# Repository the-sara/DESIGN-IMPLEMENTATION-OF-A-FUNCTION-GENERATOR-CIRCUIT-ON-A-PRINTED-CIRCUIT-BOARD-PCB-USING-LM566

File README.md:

Function Generator (PCB with LM566): Designed and built a function generator circuit using KiCad, including simulation, validation, and component selection, gaining hands-on experience in PCB design and prototyping.

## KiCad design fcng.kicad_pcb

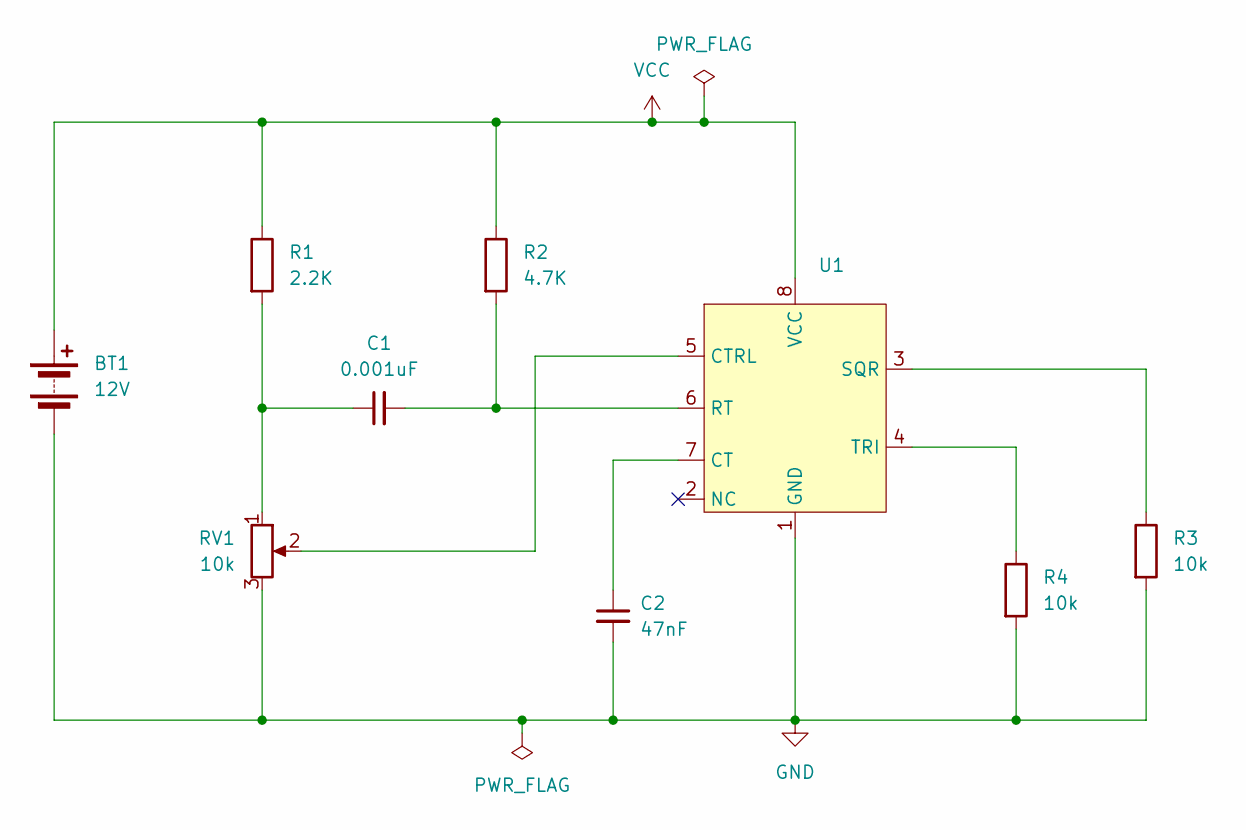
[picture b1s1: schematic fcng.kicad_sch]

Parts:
BT1: 12V; PinHeader_1x02_P2.54mm_Horizontal
C1: 0.001uF; C_Axial_L3.8mm_D2.6mm_P7.50mm_Horizontal
C2: 47nF; C_Axial_L3.8mm_D2.6mm_P7.50mm_Horizontal
R1: 2.2K; R_Axial_DIN0207_L6.3mm_D2.5mm_P10.16mm_Horizontal
R2: 4.7K; R_Axial_DIN0207_L6.3mm_D2.5mm_P10.16mm_Horizontal
R3, R4: 10k; R_Axial_DIN0207_L6.3mm_D2.5mm_P10.16mm_Horizontal
RV1: 10k; Potentiometer_Bourns_3266X_Horizontal
U1: DIP-8_W7.62mm_LongPads

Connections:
GND: BT1.2 (-), C2.2, R3.2, R4.2, RV1.3, U1.1 (GND)
unnamed: C1.1, R1.2, RV1.1
unnamed: C2.1, U1.7 (CT)
unnamed: RV1.2, U1.5 (CTRL)
unnamed: C1.2, R2.2, U1.6 (RT)
unnamed: R3.1, U1.3 (SQR)
unnamed: R4.1, U1.4 (TRI)
VCC: BT1.1 (+), R1.1, R2.1, U1.8 (VCC)

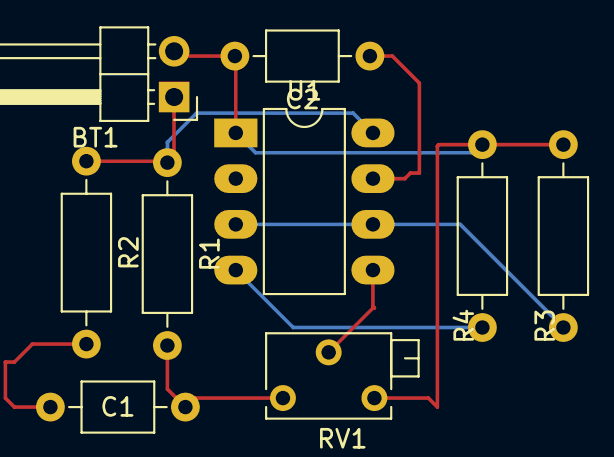
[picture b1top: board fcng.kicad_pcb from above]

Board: 2 copper layers, 9 parts (0 on the bottom side), 8 nets.
